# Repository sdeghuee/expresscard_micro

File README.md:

# expresscard_micro
A micro controller based on ATSAMD21 designed to fit inside of an express card

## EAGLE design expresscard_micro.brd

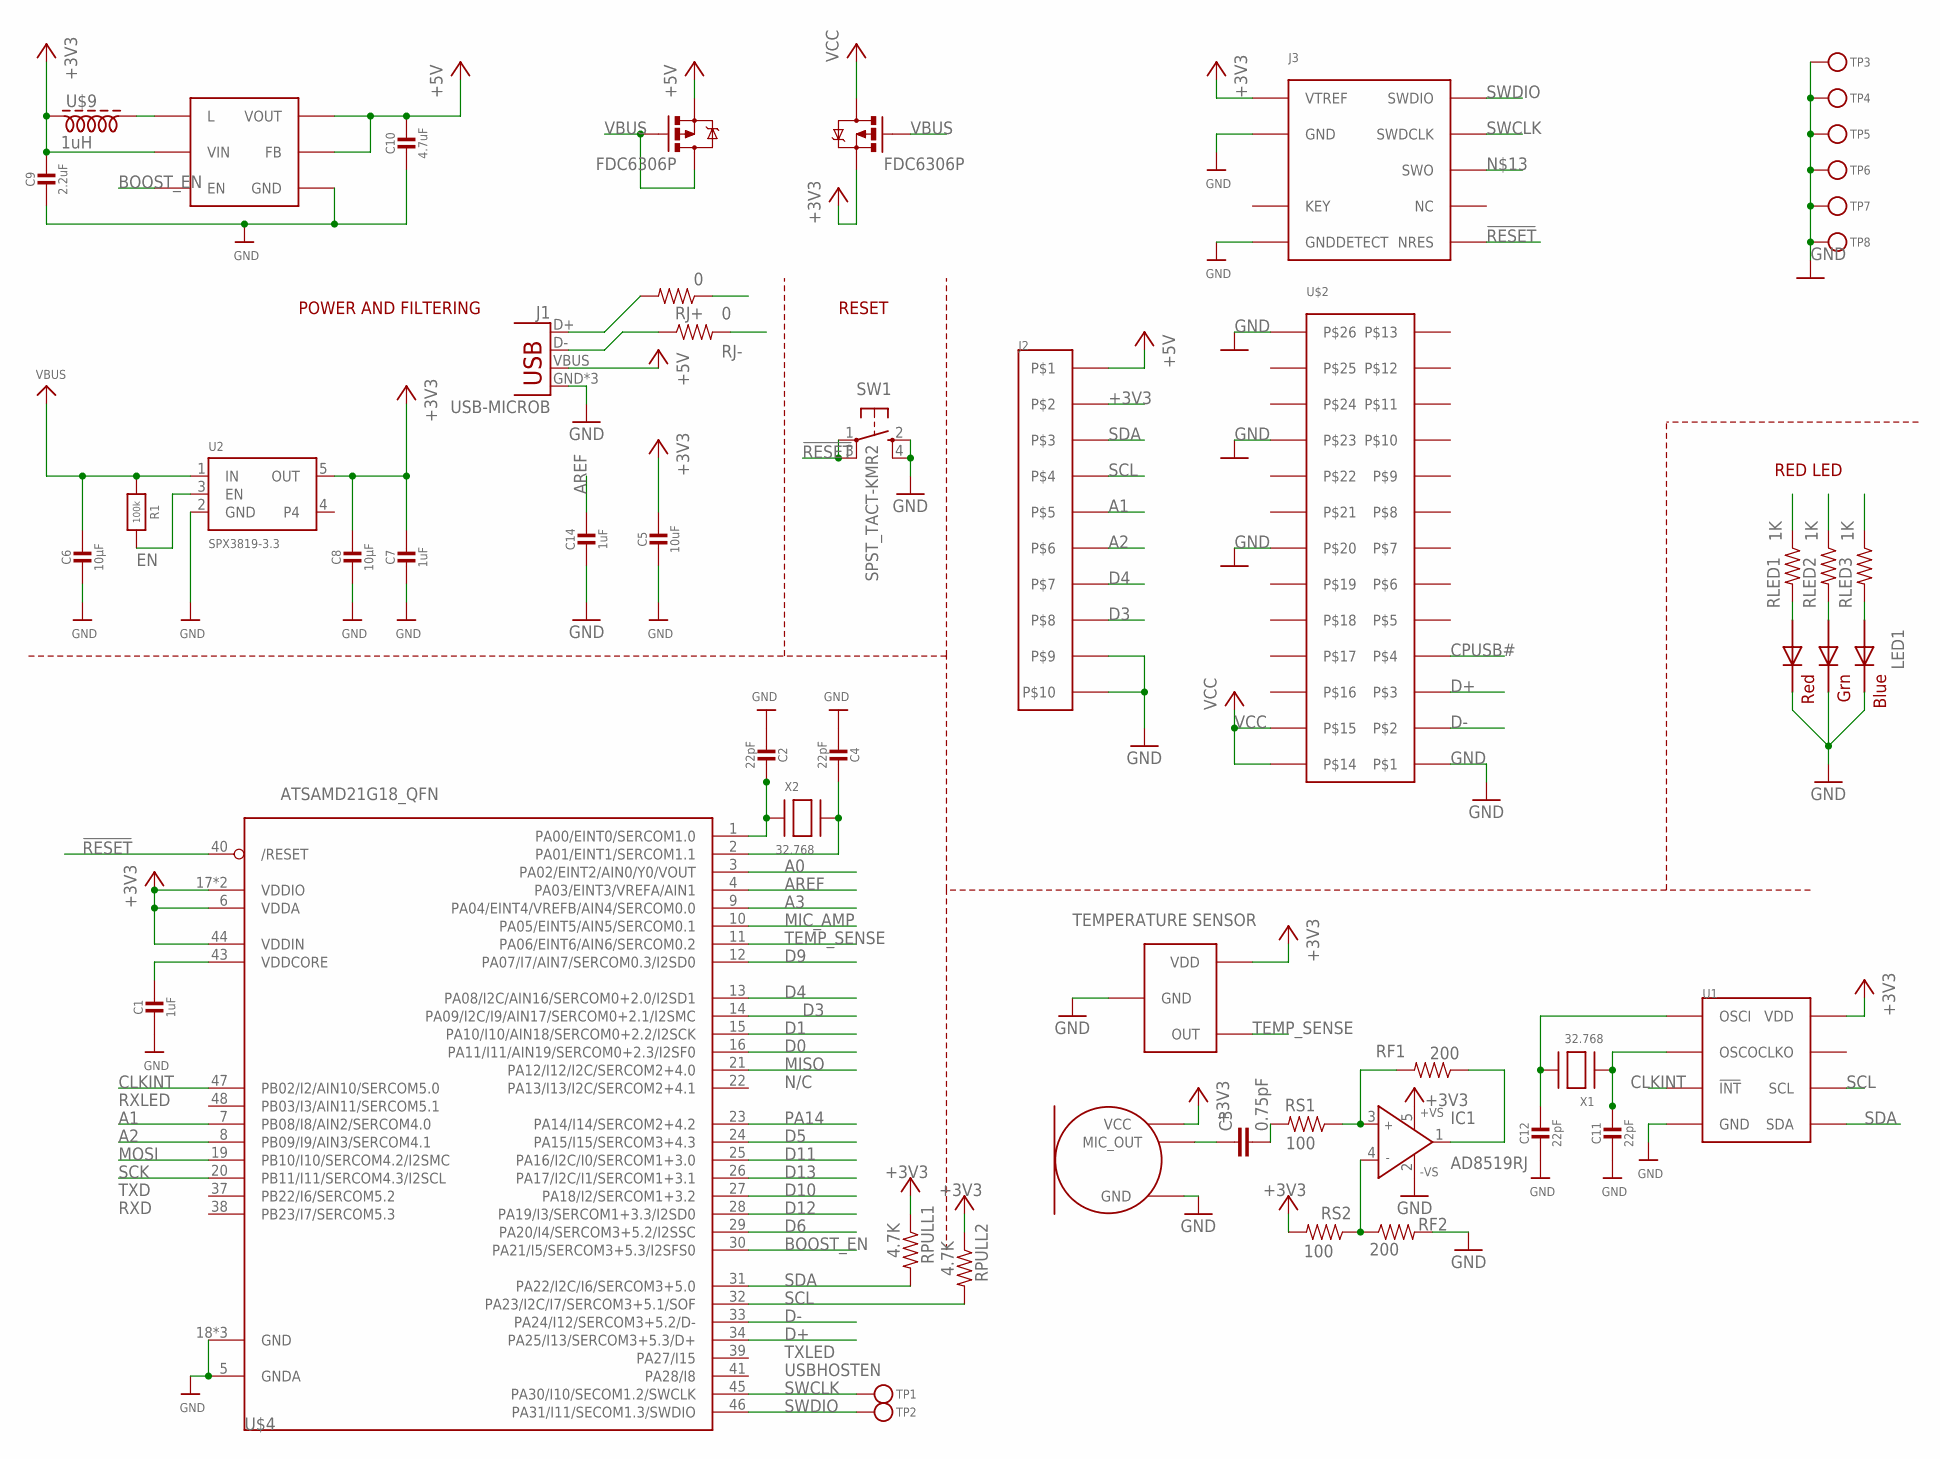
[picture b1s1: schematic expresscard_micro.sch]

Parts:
C1, C7, C14: 1uF; 0603-NO
C2, C4, C11, C12: 22pF; 0603-NO
C3: 0.75pF; 0603-CAP
C5: 10uF; 0805-NO
C6, C8: 10µF; 0805-NO
C9: 2.2uF; 0805-NO
C10: 4.7uF; 0805-NO
IC1: AD8519RJ; SOT23-5
J1: USB-MICROB
J2: FCS8_10; FCS8_10PIN
J3: JLINK_10PIN; FTSH-105-01-F-DH
LED1: RGBLED5050
R1: 100k; 0603-NO
RF1, RF2: 200; 0603-RES
RJ+: 0; 0603-RES
RJ-: 0; 0603-RES
RLED1, RLED2, RLED3: 1K; 0603-RES
RPULL1, RPULL2: 4.7K; 0603-RES
RS1, RS2: 100; 0603-RES
SW1: SPST_TACT-KMR2; KMR2
TEMPSENSE: MCP9700T-E; SOT23
TP1, TP2, TP3, TP4, TP5, TP6, TP7, TP8: TESTPOINTROUND1.5MM; TESTPOINT_ROUND_1.5MM
U1: PCF8563_RTC; SO08
U2: SPX3819-3.3; SOT23-5
U$1: SPW2430HR5H-B; 3.1_2.5_SMD
U$2: EXPRESSCARD; EXPRESSCARD_PACK
U$3: FDC6306P; SOT-23_6
U$4: ATSAMD21G18_QFN; TQFP48
U$7: TPS61240DRVR; WSON6
U$9: 1uH; 2520(1008)
X1, X2: 32.768; XTAL3215

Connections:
!RESET: J3.10 (NRES), SW1.1, SW1.3 (P1), U$4.40 (/RESET)
+3V3: C5.1, C7.1, C8.1, C9.1, IC1.5 (+VS), J2.P2, J3.1 (VTREF), RPULL1.1, RPULL2.1, RS2.2, TEMPSENSE.1 (VDD), U1.8 (VDD), U2.5 (OUT), U$1.VDD (VCC), U$3.5 (S), U$4.6 (VDDA), U$4.17 (VDDIO), U$4.36 (VDDIO), U$4.44 (VDDIN), U$7.P6 (VIN), U$9.1
+5V: C10.1, U$3.2 (S), U$7.P2 (VOUT), U$7.P3 (FB)
A0: U$4.3 (PA02/EINT2/AIN0/Y0/VOUT)
A1: J2.P5, U$4.7 (PB08/I8/AIN2/SERCOM4.0)
A2: J2.P6, U$4.8 (PB09/I9/AIN3/SERCOM4.1)
A3: U$4.9 (PA04/EINT4/VREFB/AIN4/SERCOM0.0)
AREF: C14.1, U$4.4 (PA03/EINT3/VREFA/AIN1)
BOOST_EN: U$4.30 (PA21/I5/SERCOM3+5.3/I2SFS0), U$7.P4 (EN)
CLKINT: U1.3 (!INT), U$4.47 (PB02/I2/AIN10/SERCOM5.0)
CPUSB#: U$2.P4
D0: RLED1.1, U$4.16 (PA11/I11/AIN19/SERCOM0+2.3/I2SF0)
D1: RLED2.1, U$4.15 (PA10/I10/AIN18/SERCOM0+2.2/I2SCK)
D3: J2.P8, U$4.14 (PA09/I2C/I9/AIN17/SERCOM0+2.1/I2SMC)
D4: J2.P7, U$4.13 (PA08/I2C/AIN16/SERCOM0+2.0/I2SD1)
D5: RLED3.1, U$4.24 (PA15/I15/SERCOM3+4.3)
D6: U$4.29 (PA20/I4/SERCOM3+5.2/I2SSC)
D9: U$4.12 (PA07/I7/AIN7/SERCOM0.3/I2SD0)
D10: U$4.27 (PA18/I2/SERCOM1+3.2)
D11: U$4.25 (PA16/I2C/I0/SERCOM1+3.0)
D12: U$4.28 (PA19/I3/SERCOM1+3.3/I2SD0)
D13: U$4.26 (PA17/I2C/I1/SERCOM1+3.1)
D+: RJ+.1, U$2.P3, U$4.34 (PA25/I13/SERCOM3+5.3/D+)
D-: RJ-.2, U$2.P2, U$4.33 (PA24/I12/SERCOM3+5.2/D-)
DJ+: J1.D+, RJ+.2
DJ-: J1.D-, RJ-.1
EN: R1.2, U2.3 (EN)
GND: C1.2, C2.2, C4.2, C5.2, C6.2, C7.2, C8.2, C9.2, C10.2, C11.2, C12.2, C14.2, IC1.2 (-VS), J1.GND, J1.MT1 (GND), J1.MT2 (GND), J2.P9, J2.P10, J3.3 (GND), J3.5 (GND), J3.9 (GNDDETECT), LED1.4 (BLUE_C), LED1.5 (RED_C), LED1.6 (GREEN_C), RF2.2, SW1.2 (S), SW1.4 (S1), TEMPSENSE.3 (GND), TP3.P$1, TP4.P$1, TP5.P$1, TP6.P$1, TP7.P$1, TP8.P$1, U1.4 (GND), U2.2 (GND), U$1.GND, U$1.GND2 (GND), U$2.P1, U$2.P20, U$2.P23, U$2.P26, U$4.5 (GNDA), U$4.18 (GND), U$4.35 (GND), U$4.42 (GND), U$7.P1 (GND)
MIC_AMP: IC1.1 (OUT), RF1.1, U$4.10 (PA05/EINT5/AIN5/SERCOM0.1)
MISO: U$4.21 (PA12/I12/I2C/SERCOM2+4.0)
MOSI: U$4.19 (PB10/I10/SERCOM4.2/I2SMC)
unnamed: C3.2, RS1.2
unnamed: LED1.2 (RED_A), RLED1.2
unnamed: IC1.3 (IN+), RF1.2, RS1.1
unnamed: C3.1, U$1.OUTPUT (MIC_OUT)
unnamed: C2.1, U$4.1 (PA00/EINT0/SERCOM1.0), X2.P$1
unnamed: LED1.1 (GREEN_A), RLED2.2
unnamed: C4.1, U$4.2 (PA01/EINT1/SERCOM1.1), X2.P$2
unnamed: IC1.4 (IN-), RF2.1, RS2.1
unnamed: LED1.3 (BLUE_A), RLED3.2
unnamed: U$7.P5 (L), U$9.2
unnamed: C11.1, U1.2 (OSCO), X1.P$1
unnamed: C12.1, U1.1 (OSCI), X1.P$2
PA14: U$4.23 (PA14/I14/SERCOM2+4.2)
SCK: U$4.20 (PB11/I11/SERCOM4.3/I2SCL)
SCL: J2.P4, RPULL2.2, U1.6 (SCL), U$4.32 (PA23/I2C/I7/SERCOM3+5.1/SOF)
SDA: J2.P3, RPULL1.2, U1.5 (SDA), U$4.31 (PA22/I2C/I6/SERCOM3+5.0)
SWCLK: J3.4 (SWDCLK), TP1.P$1, U$4.45 (PA30/I10/SECOM1.2/SWCLK)
SWDIO: J3.2 (SWDIO), TP2.P$1, U$4.46 (PA31/I11/SECOM1.3/SWDIO)
TEMP_SENSE: TEMPSENSE.2 (OUT), U$4.11 (PA06/EINT6/AIN6/SERCOM0.2)
VBUS: C6.1, J1.VBUS, J2.P1, R1.1, U2.1 (IN), U$3.1 (G), U$3.3 (G), U$3.4 (D)
VCC: U$2.P14, U$2.P15, U$3.6 (D)
VDDCORE: C1.1, U$4.43 (VDDCORE)

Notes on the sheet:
POWER AND FILTERING
RESET
N/C
TXLED
USBHOSTEN
RXLED
TXD
RXD
RED LED
TEMPERATURE SENSOR

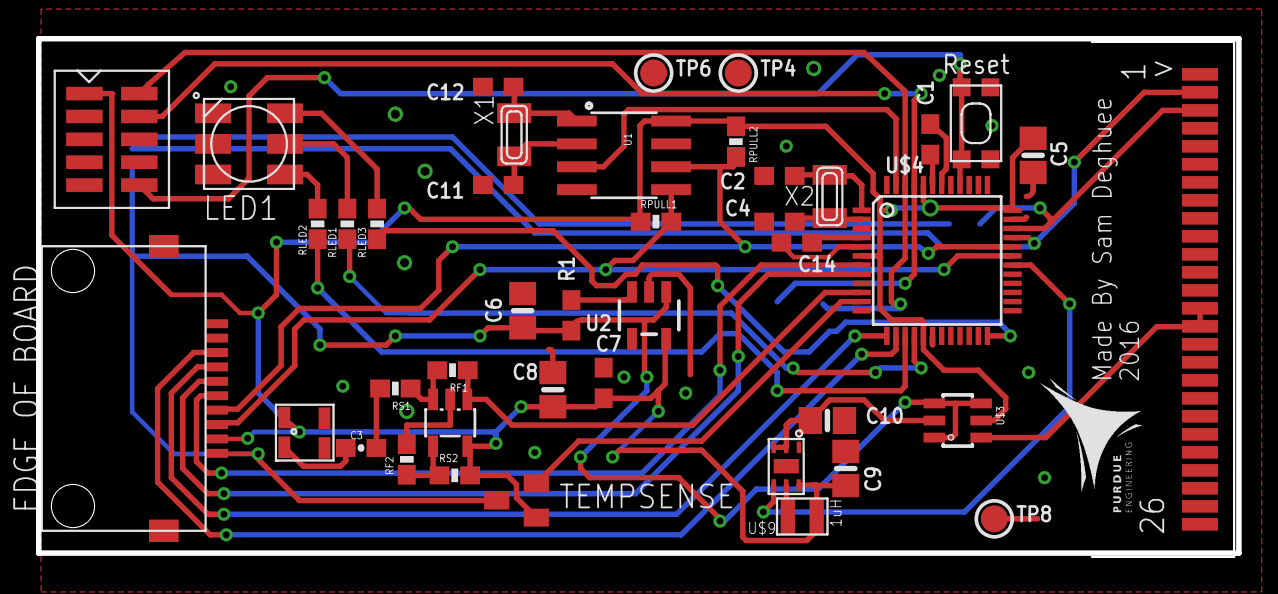
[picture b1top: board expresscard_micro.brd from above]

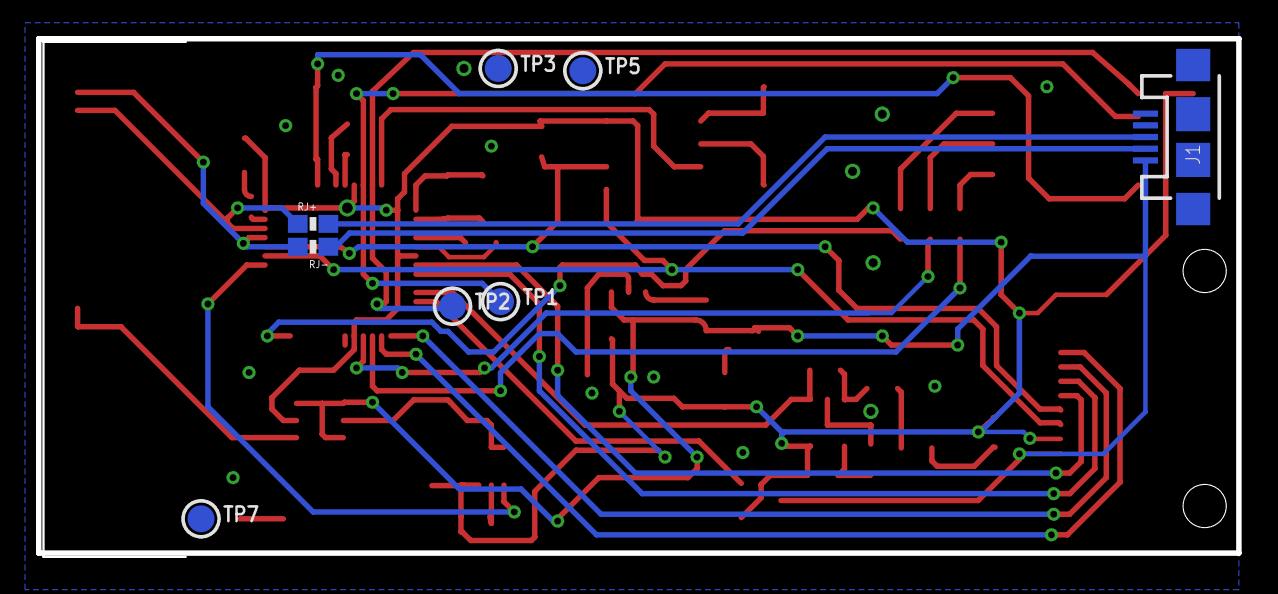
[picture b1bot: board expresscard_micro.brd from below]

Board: 2 copper layers, 66.7 x 28.7 mm, 50 parts (8 on the bottom side), 40 nets.

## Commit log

2016-12-06 Initial Upload

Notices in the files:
parts and their libraries:
microbuilder: This work is placed in the public domain, and may be freely used for commercial and non-commercial work with the following conditions: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
SparkFun-Connectors: Licensing: Creative Commons ShareAlike 4.0 International - https://creativecommons.org/licenses/by-sa/4.0
